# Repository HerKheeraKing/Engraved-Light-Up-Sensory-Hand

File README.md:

<h1 align="center">Mia-mi – Interactive Light-Up Sensory Hand</h1>

##### <p align="center"> Built from a personal sensory habit I didn’t understand until adulthood, this project blends touch and light to create a calming, tech-driven experience.
</p>

  <p align="center"> This engraved sensory hand is an interactive, light-based component designed to support neurodivergent students through touch and uses color to suggest warm-to-cool sensations.
  </p>

<div align="center">
  
</div>

# How it works:
🖐️ Touch-based interaction: Users place their fingers into engraved slots, triggering capacitive touch input through the MPR121 sensor.

🎨 Color-driven sensory feedback: LEDs transition smoothly from red → pink → purple → blue, using color to suggest warm-to-cool temperature sensations.

🧠 Sensory grounding: The slow color shift is designed to recreate a familiar, soothing hand-on-surface sensation through light and texture.

🔌 Embedded control: An ESP32 manages touch input and LED behavior, starting at blue and transitioning based on interaction timing.

🛠️ Expandable behavior: The system is designed to support future features such as real temperature feedback.

Tools: SolidWorks, Arduino (C/C++), ESP32, 3D Printing, CNC, Soldering
<br><br>

## Demo Videos  

##### 🎮 POV: Mia-mi in Action -> Click To Watch!
<p align="left">
  
</p>

<br>

##### 🎥 Mia-mi lights on Demo -> Click To Watch!
<p align="left">
  
</p>

<br><br>
📸 Additional photos documenting each build step can be found in the Solidworks/My Things/Mia-mi Images folder.

<br><br><br>
#### 📄 LICENSE INFO 
This source code is available for viewing only. Usage of the code in any form is prohibited without explicit permission. Please refer to the LICENSE file for more details.

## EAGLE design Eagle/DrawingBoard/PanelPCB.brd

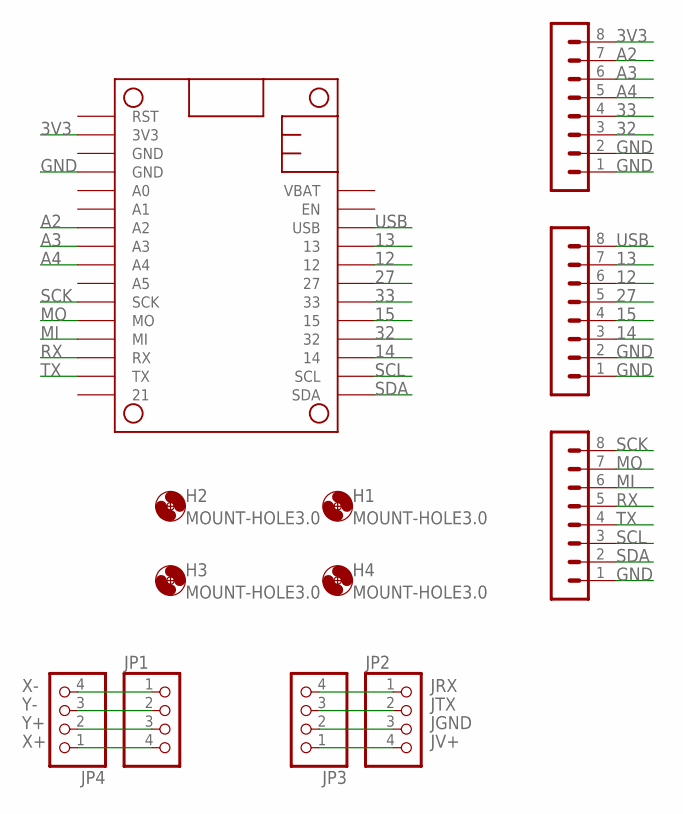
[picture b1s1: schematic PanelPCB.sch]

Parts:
H1, H2, H3, H4: MOUNT-HOLE3.0; 3,0
JP1, JP2, JP3, JP4: PINHD-1X4; 1X04
M1: RARNDT-MISCELANEOUS_FEATHERBOARD_ESP32FETHERWING_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; RARNDT-MISCELANEOUS_FEATHERBOARD_ESP32
SV1, SV2, SV3: MA08-1

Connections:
3V3: M1.2 (3V3), SV1.8
12: M1.24 (12), SV2.6
13: M1.25 (13), SV2.7
14: M1.19 (14), SV2.3
15: M1.21 (15), SV2.4
27: M1.23 (27), SV2.5
32: M1.20 (32), SV1.3
33: M1.22 (33), SV1.4
A2: M1.7 (A2), SV1.7
A3: M1.8 (A3), SV1.6
A4: M1.9 (A4), SV1.5
GND: M1.4 (GND), SV1.1, SV1.2, SV2.1, SV2.2, SV3.1
JGND: JP2.3, JP3.2
JRX: JP2.1, JP3.4
JTX: JP2.2, JP3.3
JV+: JP2.4, JP3.1
MI: M1.13 (MI), SV3.6
MO: M1.12 (MO), SV3.7
RX: M1.14 (RX), SV3.5
SCK: M1.11 (SCK), SV3.8
SCL: M1.18 (SCL), SV3.3
SDA: M1.17 (SDA), SV3.2
TX: M1.15 (TX), SV3.4
USB: M1.26 (USB), SV2.8
X+: JP1.4, JP4.1
X-: JP1.1, JP4.4
Y+: JP1.3, JP4.2
Y-: JP1.2, JP4.3

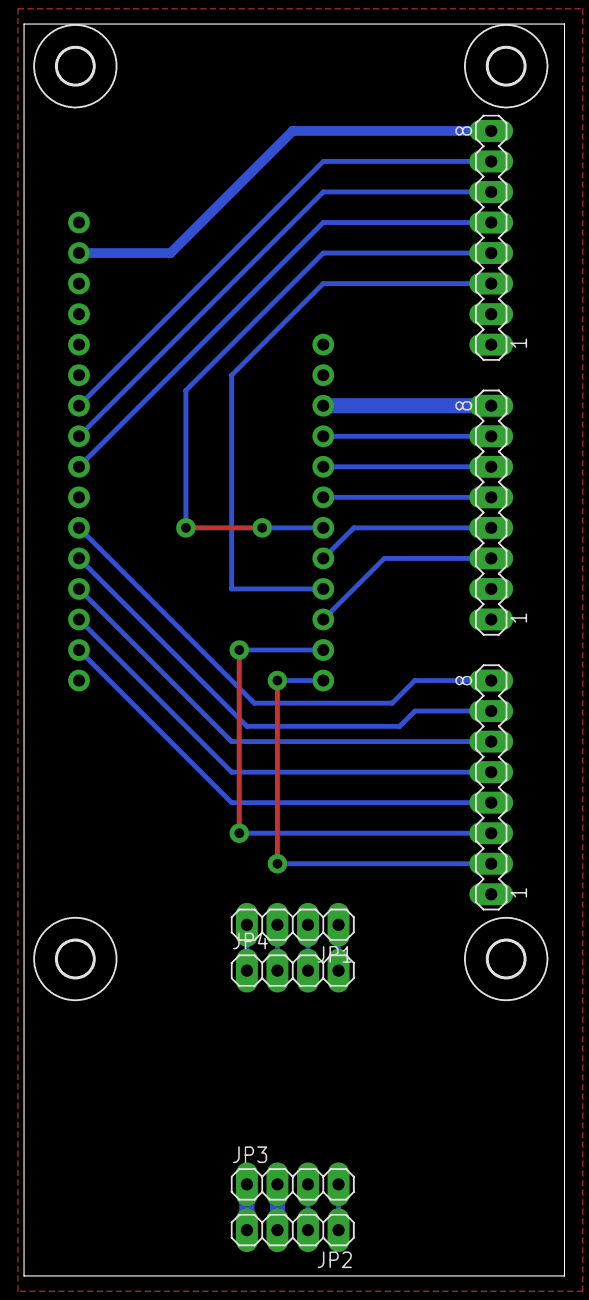
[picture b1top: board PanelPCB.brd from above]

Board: 2 copper layers, 45.0 x 104.1 mm, 12 parts (0 on the bottom side), 28 nets.

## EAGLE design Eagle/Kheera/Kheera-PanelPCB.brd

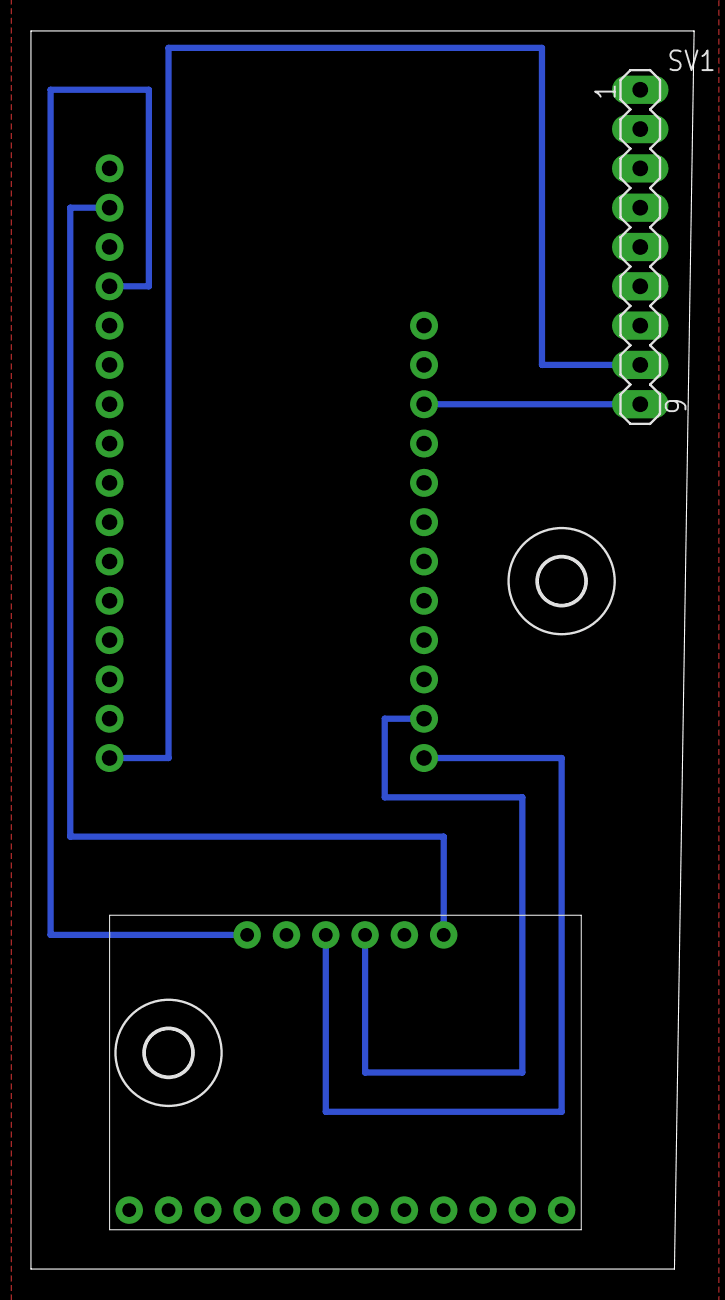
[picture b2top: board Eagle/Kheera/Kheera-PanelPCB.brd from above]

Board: 2 copper layers, 42.9 x 80.0 mm, 5 parts (0 on the bottom side), 6 nets.

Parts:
H1, H2: MOUNT-HOLE3.0; 3,0
M1: RARNDT-MISCELANEOUS_FEATHERBOARD_ESP32FETHERWING_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; RARNDT-MISCELANEOUS_FEATHERBOARD_ESP32
SV1: MA09-1
U$5: MS-121

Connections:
3V3: M1.2, U$5.3.3V
GND: M1.4, U$5.GND
unnamed: M1.16, SV1.8
SCL: M1.18, U$5.SCL
SDA: M1.17, U$5.SDA
USB: M1.26, SV1.9

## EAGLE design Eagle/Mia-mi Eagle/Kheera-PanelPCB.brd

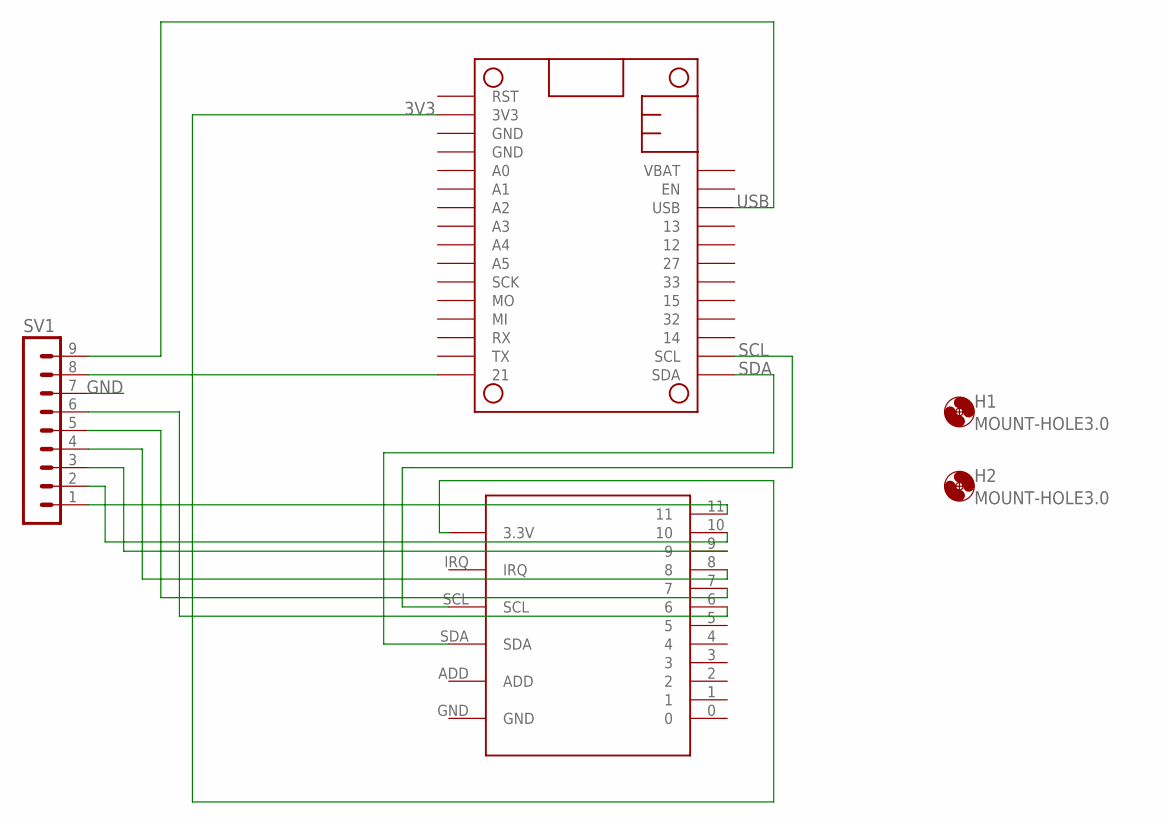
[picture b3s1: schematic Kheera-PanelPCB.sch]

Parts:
H1, H2: MOUNT-HOLE3.0; 3,0
M1: RARNDT-MISCELANEOUS_FEATHERBOARD_ESP32FETHERWING_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; RARNDT-MISCELANEOUS_FEATHERBOARD_ESP32
SV1: MA09-1
U$5: MS-121

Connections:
3V3: M1.2 (3V3), U$5.3.3V
GND: M1.4 (GND), SV1.7, U$5.GND
unnamed: M1.16 (21), SV1.8
unnamed: SV1.1, U$5.11
unnamed: SV1.2, U$5.10
unnamed: SV1.3, U$5.9
unnamed: SV1.4, U$5.8
unnamed: SV1.5, U$5.7
unnamed: SV1.6, U$5.6
SCL: M1.18 (SCL), U$5.SCL
SDA: M1.17 (SDA), U$5.SDA
USB: M1.26 (USB), SV1.9

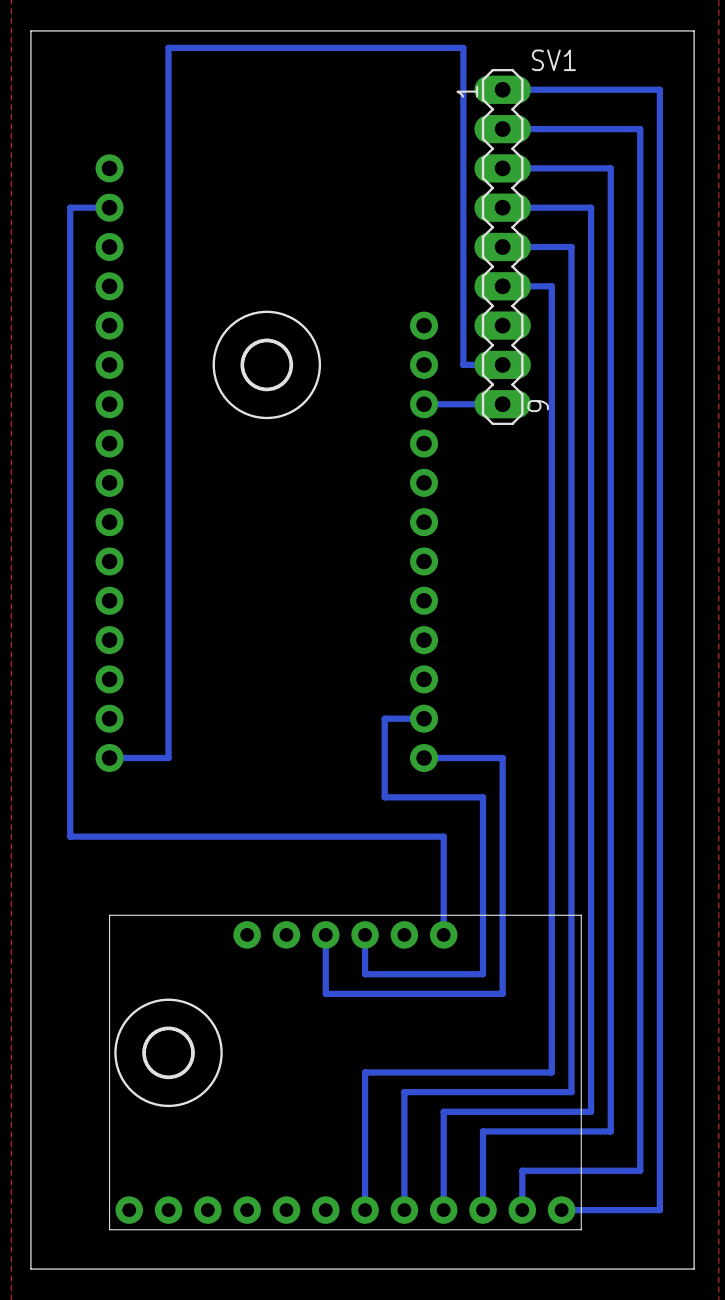
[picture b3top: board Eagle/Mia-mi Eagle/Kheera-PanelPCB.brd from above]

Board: 2 copper layers, 42.9 x 80.0 mm, 5 parts (0 on the bottom side), 12 nets.

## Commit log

2025-03-03 Initial push
2025-03-03 testing
2025-03-03 Base gitignore
2025-03-03 Removed test files
2025-03-03 Base Unity Push
2025-03-03 Upgraded versions
2025-03-04 Unity App update
2025-03-05 App done
2025-03-06 Testing bluetooth between devices (Not sure why it doesnt work)
2025-03-11 Mostly solid PanelManager library setup, there is 1 small known bug. Updated and organized the solidworks files. Made a template ino file for the panelmanager, as well as uploaded the backlit panel's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
2025-03-12 Small fixes to help stablize library/faster responses
2025-03-12 Updated Library zip
2025-03-12 Updated panel parts
2025-03-13 Added a heartbeat to handle graceful disconnects, fixed the layout so it fits mobile screens better, fixed the scrollview so the slider matches the entries and its limited to the actual users
2025-03-14 Enter repo
2025-03-14 Adding eagle files for .cam and .dru
2025-03-15 Adjusted Backlit ino to match actual panel, added master pcb sch/board and its related cam files, added mounting holes on the cover for the pcb, along with making 2 battery holders to test
2025-03-17 Updated slide-stopper to be smaller to fit battery
2025-03-17 Updated screw holes
2025-03-17 Josh S Panel Cover V2
2025-03-18 BaseCover_LightMazeV2 Imported
2025-03-18 BaseCover_JoshS_V3 STL Imported
    - Updated BaseCover SLDPRT
    - Panel Size changed from 228 to 210
    - Offset from edge of panel changed from 15 to 12
2025-03-19 Test Maze
2025-03-19 V6 Model Updated
2025-03-19 Updated parts/code and getting app to load on phone
2025-03-19 Updated PCB board to allow more clearance
2025-03-19 Final Wednesday Commit (Details in Description)
2025-03-19 Updated CAM Files
2025-03-20 V10 and V6 STL Imported
    - Added an 8th trench
2025-03-20 Updated Backlit Cover to move holes up and better line up the pot screw holes
2025-03-21 V10 Updated
    - Moved trenches and added joystick holes and layout for circuit board
    - Cut holes into the trench to provide a better way for soldering the LED's into the maze
2025-03-21 Updated light panel to be smaller and without ridges
2025-03-21 V10 Update
    - Added PCB Holes for circuit board and moved joystick
2025-03-21 V7 STL Imported
2025-03-21 Reorganization
2025-03-21 Trench Cover V1 Imported
2025-03-21 LightMaze.ino Imported
2025-03-26 LightMaze V1 Updated
2025-03-26 Updated LightMazeV1 and Imported JoystickV1 STL
2025-03-26 JoystickV2 Imported
2025-03-26 Updated JoystickV2
2025-03-26 Updated PCB design
2025-03-26 Joystick V3 Imported
2025-03-26 TestPieceV1 Imported
2025-03-26 JoystickV4 Imported
2025-03-26 Updated Front Plate
2025-03-26 BaseCover_JoshS_V11 and Joystick V5 Imported
2025-03-26 BaseCover_JoshS_V11 STL Imported
2025-03-28 Test pic inserts
2025-03-28 Animal clicker sounds to be cut
2025-03-28 BaseCover_JoshS_V11 and LightMaze.ino is updated
2025-03-28 Added trimmed sounds
2025-03-28 Insert size tests
2025-03-28 Fixed insert size tests
2025-03-28 LightMaze.ino updated
2025-03-28 Cat insert
2025-04-09 Phase 1 of Kheera's Hand Model
    > 6 1/2 Hand
    > Hand mold
    > Material thin enough for diffusing light
    > Base size: 210 x 210
    > Base needs cut out for ESP32
    > STL put to print for testing
2025-04-14 Created my solid works stuff
2025-04-14 Added drawing board files
2025-04-14 Added stl
2025-04-14 Saved and updated STLs
2025-04-14 Updated Parts
    -Created the assebmly for the backplate and basecover
    -Created the back plate
    -Updated my baseCover
    -Created my STL files
2025-04-14 Updated BehindBoard
2025-04-14 Phase 2 of Kheera's Hand Model
    - Schematic
    - Board
    - Prototype Assessment
2025-04-14 Update Parts
    -Updated to add holes to the Top Part
2025-04-14 Phase 2 of Kheera's Hand Model
    - SW Hand Model 1.0
2025-04-14 Kheera's STL
    Hand Model
2025-04-16 Face PLate STL
2025-04-16 Phase 2 of Kheera's Hand Model Final Print
    > 3D print hand model accessing
    > Redesign hand Model in Solidworks
    > Smooth fingertips
    > Test light diffusing
    > Model needs hole for cord
    > Design schematic / board
2025-04-16 4mm -> 3mm STL
2025-04-21 Drawing board extra stls
2025-04-21 Kheera - Final Board Cut Design
2025-04-21 ok, final final design board kheera
2025-04-23 Eagle files
2025-04-23 Updated DrawingBoard eagle files for cutting/printing
2025-04-23 keycap!
2025-04-23 keycap
2025-04-23 Phase 3 Logic for Code Updated
2025-04-24 Drawing board code updated
2025-04-28 Modified drawing board files
2025-04-28 Phase 3 Completion
    - Assembled Physical Components
    - Added lerping logic to code
2025-04-30 Cleaned Git / Folders
    - Created individual folders for each category ( SW, Arduino, Eagle )
    - Removed unnecessary files
2026-01-14 Added mia mi images
2026-01-14 Transparent hand model
2026-01-14 Update final 4 image (cropped)
2026-01-14 Photo name change
2026-01-14 Added jacob demo video
